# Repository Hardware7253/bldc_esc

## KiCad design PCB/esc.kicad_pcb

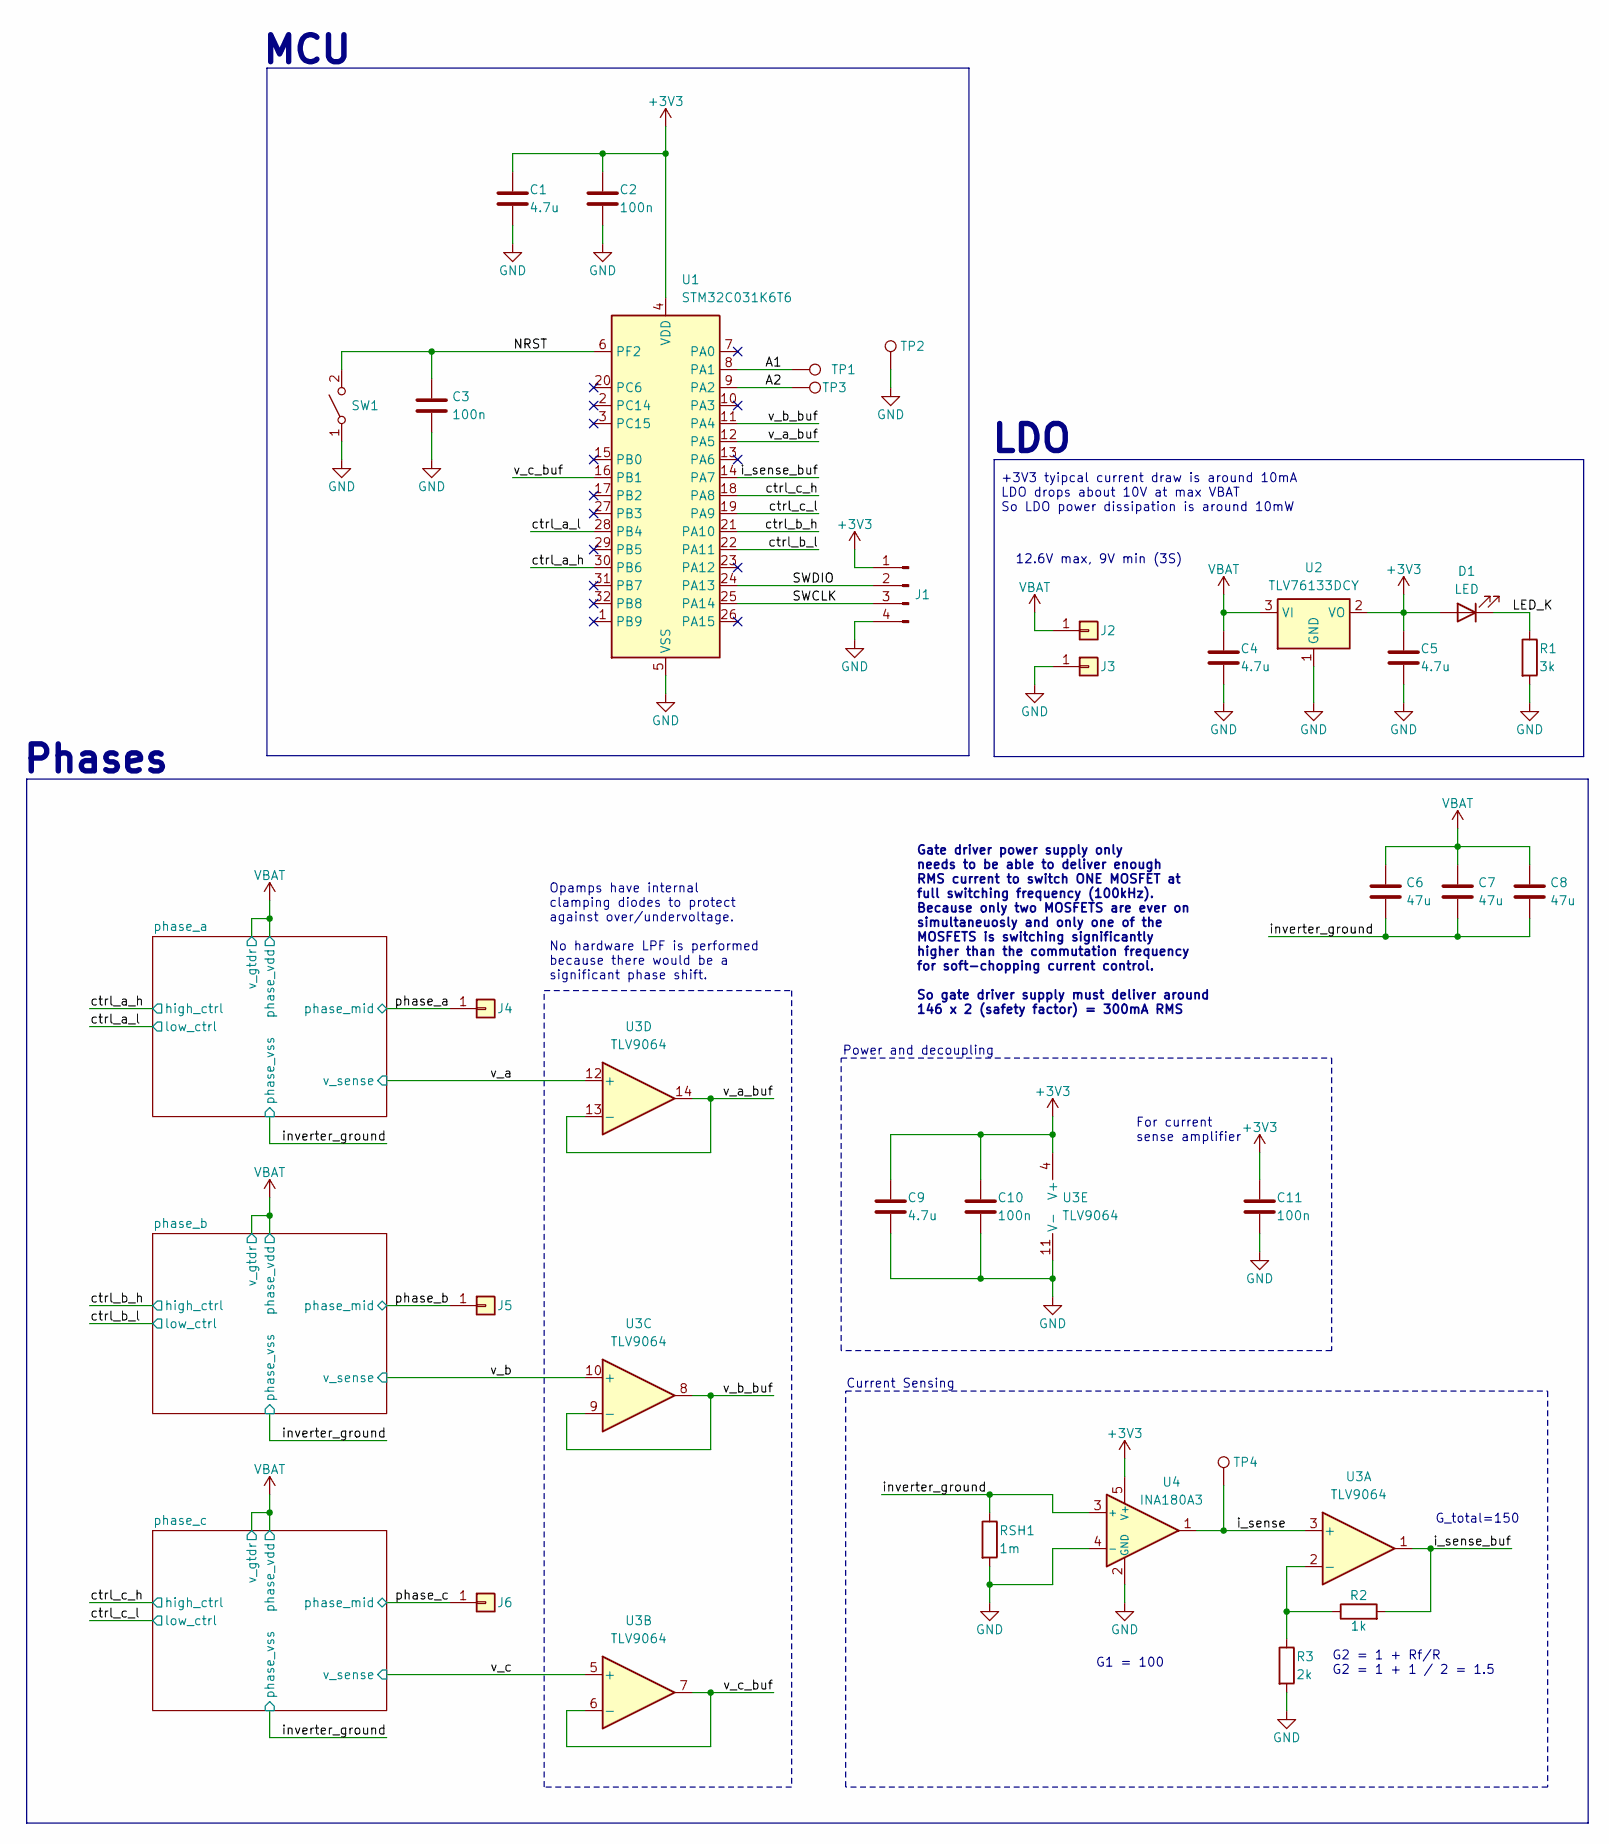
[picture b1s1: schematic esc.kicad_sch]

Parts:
C1, C4, C5, C9: 4.7u; C_0603_1608Metric; LCSC Part No. C1705
C2, C3, C10, C11: 100n; C_0603_1608Metric; LCSC Part No. C14663
C6, C7, C8: 47u; C_1206_3216Metric; LCSC Part No. C6119972
D1: LED; LED_0603_1608Metric; LCSC Part No. C2286
J1: Conn_01x04_Pin; PinHeader_1x04_P1.27mm_Vertical_SMD_Pin1Right; LCSC Part No. C41375974
J2, J3, J4, J5, J6: Conn_01x01; TestPoint_Pad_2.5x2.5mm
R1: 3k; R_0603_1608Metric; LCSC Part No. C2907033
R2: 1k; R_0603_1608Metric; LCSC Part No. C22548
R3: 2k; R_0603_1608Metric; LCSC Part No. C22975
RSH1: 1m; R_2512_6332Metric; LCSC Part No. C46634444
SW1: SW_SPST; SW_SPST_CK_RS282G05A3; LCSC Part No. C118141
TP1, TP2, TP3, TP4: TestPoint; TestPoint_Pad_D1.5mm
U1: STM32C031K6T6; LQFP-32_7x7mm_P0.8mm; LCSC Part No. C5456169
U2: TLV76133DCY; SOT-223-3_TabPin2; LCSC Part No. C7527500
U3: TLV9064; TSSOP-14_4.4x5mm_P0.65mm; LCSC Part No. C779410
U4: INA180A3; SOT-23-5; LCSC Part No. C2877844

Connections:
+3V3: C1.1, C2.1, C5.1, C9.1, C10.1, C11.1, D1.2 (A), J1.1, U1.4 (VDD), U2.2 (VO), U3.4 (V+), U4.5 (V+)
/A1: TP1.1 (1_1), U1.8 (PA1)
/A2: TP3.1 (1_1), U1.9 (PA2)
/LED_K: D1.1 (K), R1.1
/NRST: C3.1, SW1.2 (B), U1.6 (PF2)
/SWCLK: J1.3, U1.25 (PA14)
/SWDIO: J1.2, U1.24 (PA13)
/ctrl_a_h: U1.30 (PB6); also elsewhere on the board
/ctrl_a_l: U1.28 (PB4); also elsewhere on the board
/ctrl_b_h: U1.21 (PA10); also elsewhere on the board
/ctrl_b_l: U1.22 (PA11); also elsewhere on the board
/ctrl_c_h: U1.18 (PA8); also elsewhere on the board
/ctrl_c_l: U1.19 (PA9); also elsewhere on the board
/i_sense: TP4.1 (1_1), U3.3 (+), U4.1
/i_sense_buf: R2.2, U1.14 (PA7), U3.1
/inverter_ground: C6.2, C7.2, C8.2, RSH1.1, U4.3 (+); also elsewhere on the board
/phase_a: J4.1 (Pin_1_1); also elsewhere on the board
/phase_b: J5.1 (Pin_1_1); also elsewhere on the board
/phase_c: J6.1 (Pin_1_1); also elsewhere on the board
/v_a: U3.12 (+); also elsewhere on the board
/v_a_buf: U1.12 (PA5), U3.13 (-), U3.14
/v_b: U3.10 (+); also elsewhere on the board
/v_b_buf: U1.11 (PA4), U3.8, U3.9 (-)
/v_c: U3.5 (+); also elsewhere on the board
/v_c_buf: U1.16 (PB1), U3.6 (-), U3.7
GND: C1.2, C2.2, C3.2, C4.2, C5.2, C9.2, C10.2, C11.2, J1.4, J3.1 (Pin_1_1), R1.2, R3.2, RSH1.2, SW1.1 (A), TP2.1 (1_1), U1.5 (VSS), U2.1 (GND), U3.11 (V-), U4.2 (GND), U4.4 (-); also elsewhere on the board
unnamed: R2.1, R3.1, U3.2 (-)
VBAT: C4.1, C6.1, C7.1, C8.1, J2.1 (Pin_1_1), U2.3 (VI); also elsewhere on the board

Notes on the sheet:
Current Sensing
G2 = 1 + Rf/R G2 = 1 + 1 / 2 = 1.5
MCU
For current sense amplifier
+3V3 tyipcal current draw is around 10mA LDO drops about 10V at max VBAT So LDO power dissipation is around 10mW
LDO
G1 = 100
G_total=150
Phases
Gate driver power supply only needs to be able to deliver enough RMS current to switch ONE MOSFET at full switching frequency (100kHz). Because only two MOSFETS are ever on simultaneuosly and only one of the MOSFETS is switching significantly higher than the commutation frequency for soft-chopping 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
12.6V max, 9V min (3S)
Opamps have internal clamping diodes to protect against over/undervoltage. No hardware LPF is performed because there would be a significant phase shift.
Power and decoupling

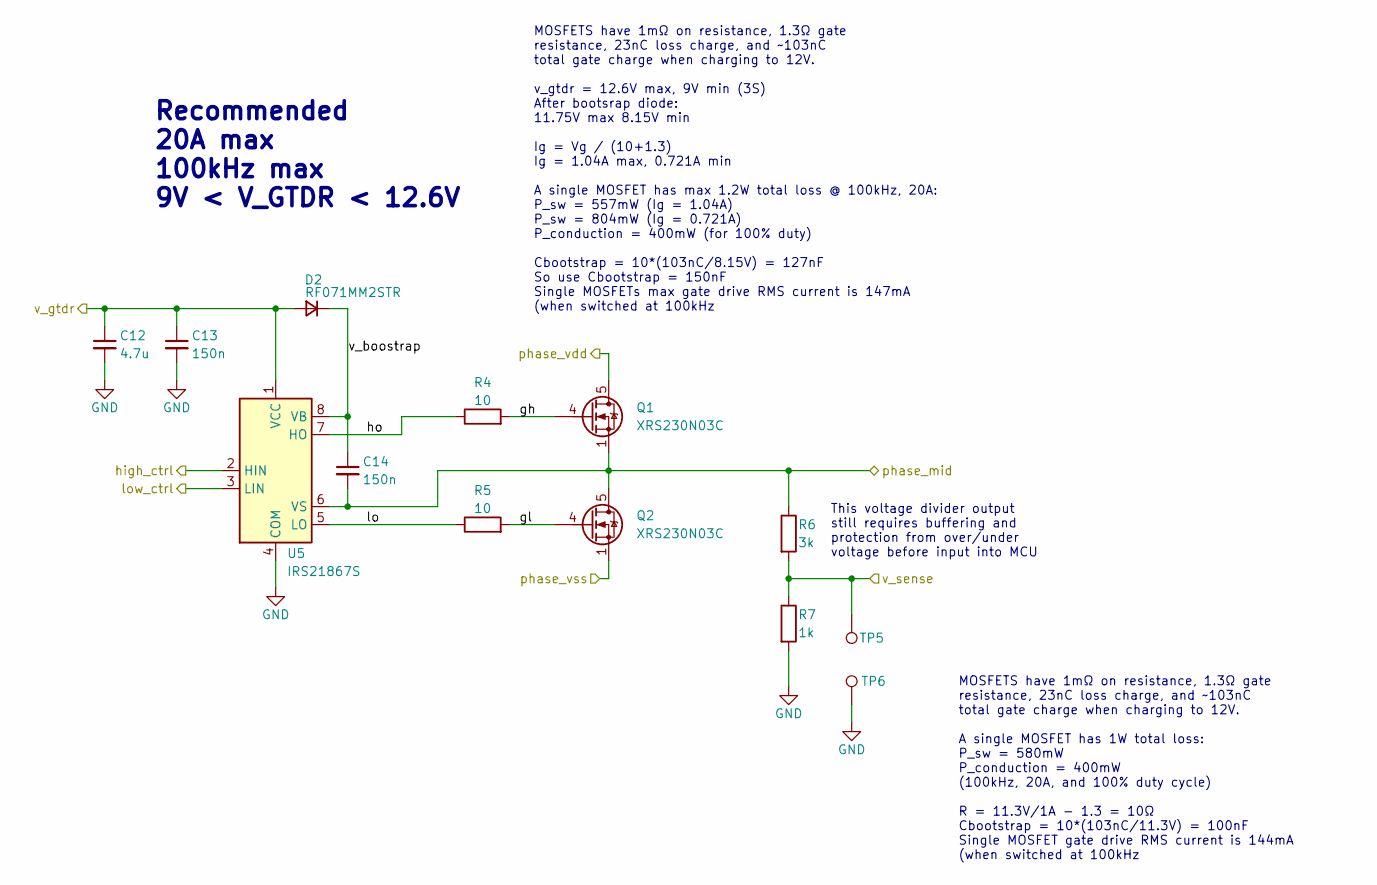
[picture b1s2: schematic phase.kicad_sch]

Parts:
C12: 4.7u; C_0603_1608Metric; LCSC Part No. C1705
C13, C14: 150n; C_0603_1608Metric; LCSC Part No. C513735
D2: RF071MM2STR; D_SOD-123; LCSC Part No. C253520
Q1, Q2: XRS230N03C; PQFN-8-EP_6x5mm_P1.27mm_Generic; LCSC Part No. C53069585
R4, R5: 10; R_0603_1608Metric; LCSC Part No. C844919
R6: 3k; R_0603_1608Metric; LCSC Part No. C2907033
R7: 1k; R_0603_1608Metric; LCSC Part No. C22548
TP5, TP6: TestPoint; TestPoint_Pad_D1.5mm
U5: IRS21867S; SOIC-8_3.9x4.9mm_P1.27mm; LCSC Part No. C20623204

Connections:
/ctrl_a_h: U5.2 (HIN); also elsewhere on the board
/ctrl_a_l: U5.3 (LIN); also elsewhere on the board
/inverter_ground: Q2.1 (S), Q2.2 (S), Q2.3 (S); also elsewhere on the board
/phase_a: C14.2, Q1.1 (S), Q1.2 (S), Q1.3 (S), Q2.5 (D), R6.1, U5.6 (VS); also elsewhere on the board
/phase_a/gh: Q1.4 (G), R4.2
/phase_a/gl: Q2.4 (G), R5.2
/phase_a/ho: R4.1, U5.7 (HO)
/phase_a/lo: R5.1, U5.5 (LO)
/phase_a/v_boostrap: C14.1, D2.1 (K), U5.8 (VB)
/v_a: R6.2, R7.1, TP5.1 (1_1); also elsewhere on the board
GND: C12.2, C13.2, R7.2, TP6.1 (1_1), U5.4 (COM); also elsewhere on the board
VBAT: C12.1, C13.1, D2.2 (A), Q1.5 (D), U5.1 (VCC); also elsewhere on the board

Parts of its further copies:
C15, C18: 4.7u; C_0603_1608Metric; LCSC Part No. C1705
C16, C17, C19, C20: 150n; C_0603_1608Metric; LCSC Part No. C513735
D3, D4: RF071MM2STR; D_SOD-123; LCSC Part No. C253520
Q3, Q4, Q5, Q6: XRS230N03C; PQFN-8-EP_6x5mm_P1.27mm_Generic; LCSC Part No. C53069585
R8, R9, R12, R13: 10; R_0603_1608Metric; LCSC Part No. C844919
R10, R14: 3k; R_0603_1608Metric; LCSC Part No. C2907033
R11, R15: 1k; R_0603_1608Metric; LCSC Part No. C22548
TP7, TP8, TP9, TP10: TestPoint; TestPoint_Pad_D1.5mm
U6, U7: IRS21867S; SOIC-8_3.9x4.9mm_P1.27mm; LCSC Part No. C20623204

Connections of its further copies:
/ctrl_b_h: U6.2 (HIN); also elsewhere on the board
/ctrl_b_l: U6.3 (LIN); also elsewhere on the board
/ctrl_c_h: U7.2 (HIN); also elsewhere on the board
/ctrl_c_l: U7.3 (LIN); also elsewhere on the board
/inverter_ground: Q4.1 (S), Q4.2 (S), Q4.3 (S), Q6.1 (S), Q6.2 (S), Q6.3 (S); also elsewhere on the board
/phase_b: C17.2, Q3.1 (S), Q3.2 (S), Q3.3 (S), Q4.5 (D), R10.1, U6.6 (VS); also elsewhere on the board
/phase_b/gh: Q3.4 (G), R8.2
/phase_b/gl: Q4.4 (G), R9.2
/phase_b/ho: R8.1, U6.7 (HO)
/phase_b/lo: R9.1, U6.5 (LO)
/phase_b/v_boostrap: C17.1, D3.1 (K), U6.8 (VB)
/phase_c: C20.2, Q5.1 (S), Q5.2 (S), Q5.3 (S), Q6.5 (D), R14.1, U7.6 (VS); also elsewhere on the board
/phase_c/gh: Q5.4 (G), R12.2
/phase_c/gl: Q6.4 (G), R13.2
/phase_c/ho: R12.1, U7.7 (HO)
/phase_c/lo: R13.1, U7.5 (LO)
/phase_c/v_boostrap: C20.1, D4.1 (K), U7.8 (VB)
/v_b: R10.2, R11.1, TP7.1 (1_1); also elsewhere on the board
/v_c: R14.2, R15.1, TP9.1 (1_1); also elsewhere on the board
GND: C15.2, C16.2, C18.2, C19.2, R11.2, R15.2, TP8.1 (1_1), TP10.1 (1_1), U6.4 (COM), U7.4 (COM); also elsewhere on the board
VBAT: C15.1, C16.1, C18.1, C19.1, D3.2 (A), D4.2 (A), Q3.5 (D), Q5.5 (D), U6.1 (VCC), U7.1 (VCC); also elsewhere on the board

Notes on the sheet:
Recommended 20A max 100kHz max 9V < V_GTDR < 12.6V
This voltage divider output still requires buffering and protection from over/under voltage before input into MCU
MOSFETS have 1mΩ on resistance, 1.3Ω gate resistance, 23nC loss charge, and ~103nC total gate charge when charging to 12V. v_gtdr = 12.6V max, 9V min (3S) After bootsrap diode: 11.75V max 8.15V min Ig = Vg / (10+1.3) Ig = 1.04A max, 0.721A min A single MOSFET has max 1.2W total loss @ 100kHz, 20A: 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
MOSFETS have 1mΩ on resistance, 1.3Ω gate resistance, 23nC loss charge, and ~103nC total gate charge when charging to 12V. A single MOSFET has 1W total loss: P_sw = 580mW P_conduction = 400mW (100kHz, 20A, and 100% duty cycle) R = 11.3V/1A - 1.3 = 10Ω Cbootstrap = 10*(103nC/11.3V) = 100nF Single MO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

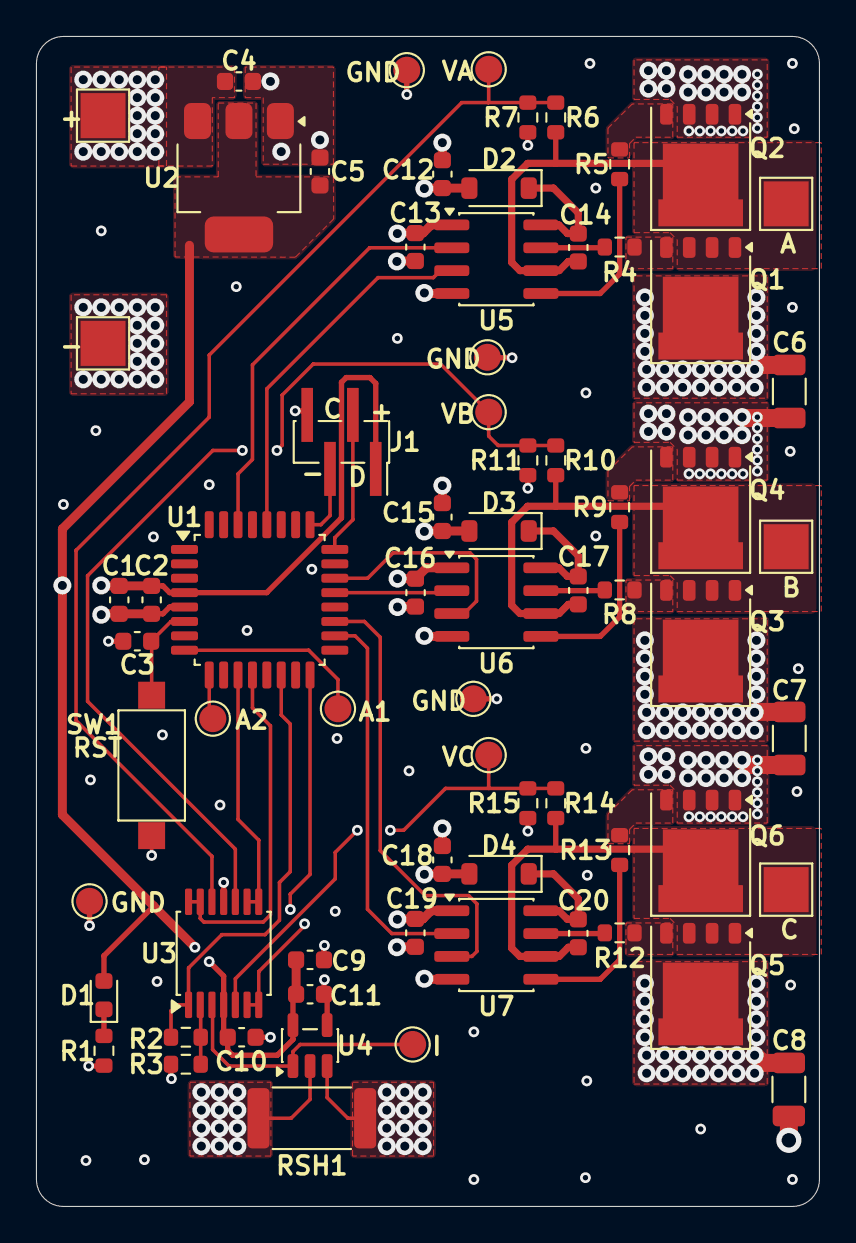
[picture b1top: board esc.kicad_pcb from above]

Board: 4 copper layers, 43.5 x 65.0 mm, 70 parts (0 on the bottom side), 43 nets.

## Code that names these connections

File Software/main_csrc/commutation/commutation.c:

#include "commutation.h"
#include "gate_drive.h"
#include "stm32c0xx_hal.h"
#include <stdint.h>

static bool forward_rotation = true; 
static commutation_step_t current_step = STEP_NULL; 
static phase_idx_t floating_phase = PHASE_NULL;

// Delay between open-loop commutation steps
// static int16_t ol_step_delay = 10; // ms

// static const int16_t ol_ramp_step = 1;      // How much to decrement by after each electrical cycle
// static const int16_t ol_step_target = 1;    // Final steady-state target

// Delay between open-loop commutation steps
static int32_t ol_step_delay = 5000;

static const int32_t ol_ramp_step = 2;      // How much to decrement by after each electrical cycle
static const int32_t ol_step_target = 2000;    // Final steady-state target

// Get the floating phase using commutation_step_t as an index
static const phase_idx_t FLOATING_PHASE_LUT[NO_COMMUTATION_STEPS] = {PHASE_C, PHASE_B, PHASE_A, PHASE_C, PHASE_B, PHASE_A};

static bool new_commutation_step = false;

inline phase_idx_t get_floating_phase(void) {
    return floating_phase;
}

// Return true if the commutation step just changed
bool did_commutation_just_step(void) {
    if (new_commutation_step) {
        new_commutation_step = false;
        return true;
    }
    return false;
}

// Changes active inverter phase pair to the next step
void next_step(void) {
    if (forward_rotation) {
        current_step++;
    } else {
        current_step--;
    }

    // Wrap around counting
    if (current_step == STEP_NULL)
        current_step = NO_COMMUTATION_STEPS - 1;
    else if(current_step == NO_COMMUTATION_STEPS)
        current_step = STEP_NULL + 1; 
    
    floating_phase = FLOATING_PHASE_LUT[current_step];
    switch_active_phases(current_step);
    new_commutation_step = true;
}

static void delay(uint32_t cycles) {
    for (volatile uint32_t i = 0; i < cycles; i++) {
        (void) i;
    }
}

// Blocking open-loop commutation
// Blocks for a full electrical cycle
void blocking_ol_commutation(void) {
    for (int i = 0; i < NO_COMMUTATION_STEPS; i++) {
        // HAL_Delay((uint32_t)ol_step_delay);
        delay((uint32_t)ol_step_delay);
        next_step();
    }

    // Decrement and clamp delay
    ol_step_delay -= ol_ramp_step;
    if (ol_step_delay < ol_step_target) {
        ol_step_delay = ol_step_target;
    }
}
